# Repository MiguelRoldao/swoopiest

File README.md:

# The Swoopiest

A keyboard based on the iconic [Swoop]() and the adored [Kyria]().

## Gudhowboutya?

## Features
* Soldered universal switch footprint (not hot-swappable)
* Reversible PCB
* Per-key RGB LEDs (mini-e)
* RGB LED underglow
* Up to 2 encoders
* Oled screens
* Power switch for battery management
* Bluetooth support w/ nice!nano or nrf52840
* Tenting puck compatible
* M5 screw holes for cheap tenting

## Components list

To build and use *The Swoopiest* you will need:

* 2× Reversible PCBs
* 2× ProMicro compatible boards or 2 nice!nanos (for headers, the [nrf52840 repo](https://github.com/joric/nrfmicro/wiki/Sockets#machine-pins) has great info)
* 40-42× Keyboard switches
* 40-42× Keycaps 1u
* 40-42× SK6812 Mini-E RGB SMD Leds (optional; not recommended for wireless)
* 40-42× SK6812 3535 RGB SMD Leds (optional; not recommended for wireless)
* 42× diodes (Surface-mount or Through-hole)
* 0-2× Rotary encoders & knobs (optional; ALPS EC11)
* 0-2× OLED LCD Display 128x64 SSD1306 (optional)
* 2× reset switches (optional; (3x6x4.3mm))
* Some little rubber feet/bumpers
* 2× power switches (wireless only; MSK 12C02)
* 2× lipo batteries (wireless only)
* 1× TRRS (See below for more) cable (wired only)
* 2× TRRS Jack [PJ-320A] (wired only)
* 1× USB Cable (depends on your micro-controller choice)  

## Switch compatibility

The universal foot print makes switch incompatibility a thing of the past. The Swoopiest is compatible with most common switch types:
* Choc v1
* Choc v2
* Gateron KS33
* Cherry MX (altough with a bit too much wiggle room. The 5-pin variation fits more snuggly)

With a bit of effort, Reddragon's low profiles also fit by twisting the legs a little bit.

#### The middle pin

The middle pin of the PCB isn't connected to anything (to allow the reversible pcb in conjunction with the universal footprint).
If switches that use the middle pin are chosen (like chocs or reddragons), connect the middle pin to the pads opposite ot the other used pin.
Whether by use of a tiny piece of wire, or with a solder blob.

## Firmware

The firmware is available in my QMK repo as `diaffractus/swoopiest`.  
You can get started by using QMK's [online configurator](https://config.qmk.fm/#/bluebell/swoop/LAYOUT_split_3x5_3). Or check [The Swoopiest README file](https://github.com/MiguelRoldao/qmk-home/blob/master/keyboards/diaffractus/swoopiest/readme.md) to see how to compile the firmware locally.

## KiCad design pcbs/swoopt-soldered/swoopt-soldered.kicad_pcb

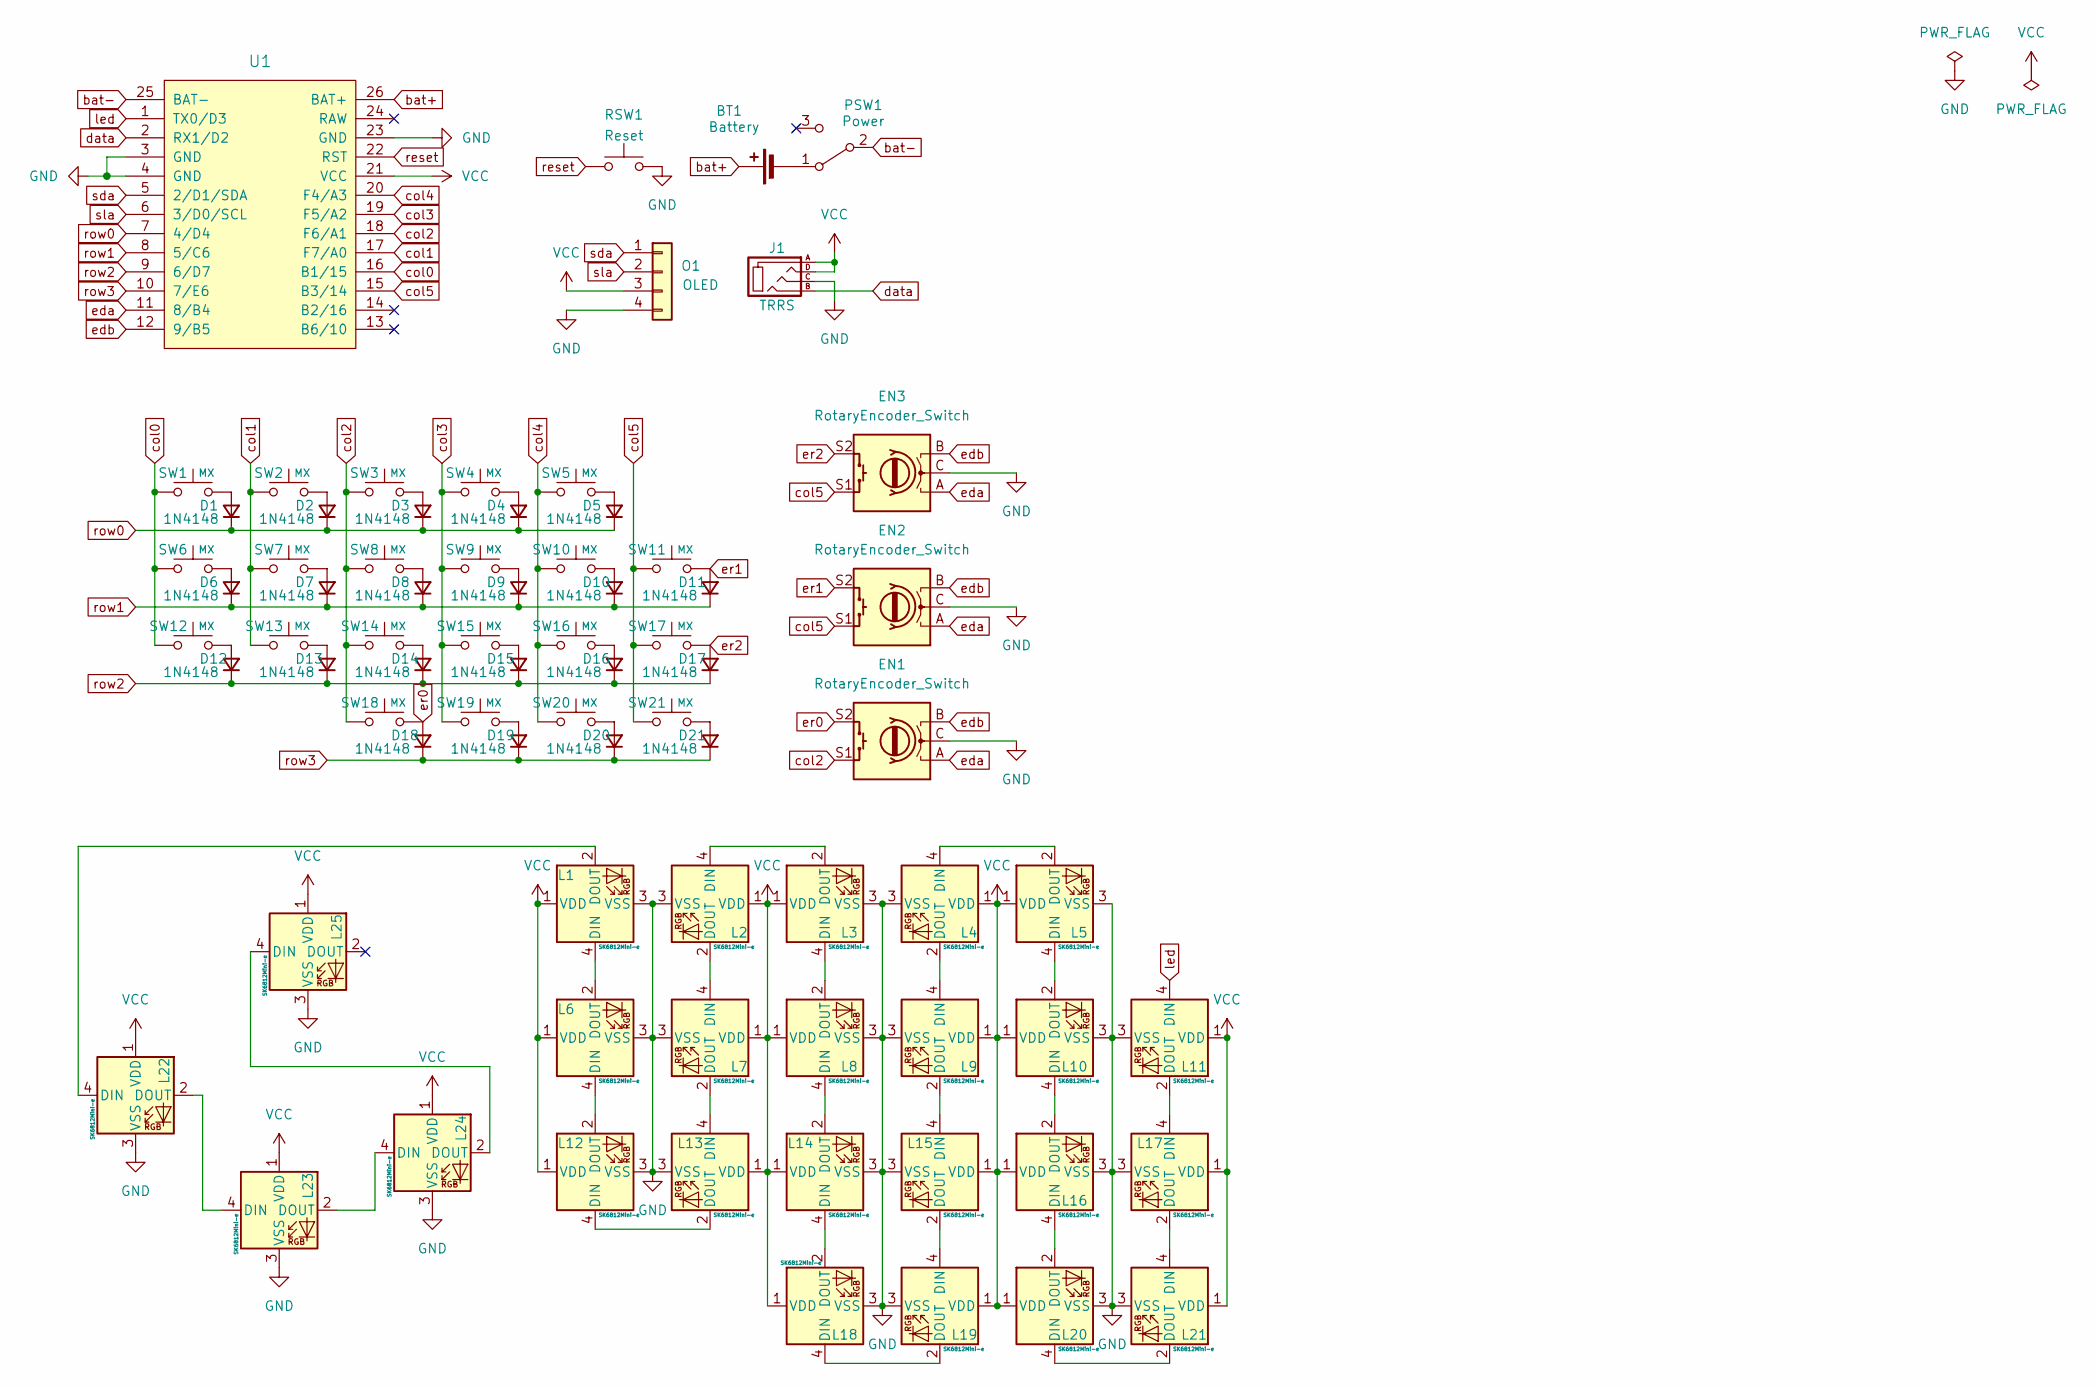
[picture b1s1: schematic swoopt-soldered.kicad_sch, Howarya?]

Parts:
BT1: Battery; Battery_pads_reversible
D1, D2, D3, D4, D5, D6, D7, D8, D9, D10, D11, D12, D13, D14, D15, D16, D17, D18, D19, D20, D21: 1N4148; D_SMD_TH
EN1, EN2, EN3: RotaryEncoder_Switch; RotaryEncoder
J1: TRRS; TRRS-3pin
L1, L2, L3, L4, L5, L6, L7, L8, L9, L10, L11, L12, L13, L14, L15, L16, L17, L18, L19, L20, L21: SK6812Mini-e; SK6812_Mini_E; JLCPCB BOM 0
L22, L23, L24, L25: SK6812Mini-e; LED_SK6812MINI__3.5x3.5mm_reversible; JLCPCB BOM 0
O1: OLED; OLED_jumpers
PSW1: Power
RSW1: Reset; SW_TH_1TS002A
SW1, SW2, SW3, SW4, SW5, SW6, SW7, SW8, SW9, SW10, SW11, SW12, SW13, SW14, SW15, SW16, SW17, SW18, SW19, SW20, SW21: MX; SW_Universal_TH_Reversible
U1: U_ProMicro_nRF52840_TH_Reversible

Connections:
GND: EN1.C, EN2.C, EN3.C, J1.C, L1.3 (VSS), L2.3 (VSS), L3.3 (VSS), L4.3 (VSS), L5.3 (VSS), L6.3 (VSS), L7.3 (VSS), L8.3 (VSS), L9.3 (VSS), L10.3 (VSS), L11.3 (VSS), L12.3 (VSS), L13.3 (VSS), L14.3 (VSS), L15.3 (VSS), L16.3 (VSS), L17.3 (VSS), L18.3 (VSS), L19.3 (VSS), L20.3 (VSS), L21.3 (VSS), L22.3 (VSS), L23.3 (VSS), L24.3 (VSS), L25.3 (VSS), O1.4, RSW1.2, U1.3 (GND), U1.4 (GND), U1.23 (GND); also elsewhere on the board
unnamed: BT1.2 (-), PSW1.1 (A)
unnamed: D1.2 (A), SW1.2
unnamed: D2.2 (A), SW2.2
unnamed: D3.2 (A), SW3.2
unnamed: D4.2 (A), SW4.2
unnamed: D5.2 (A), SW5.2
unnamed: D6.2 (A), SW6.2
unnamed: D7.2 (A), SW7.2
unnamed: D8.2 (A), SW8.2
unnamed: D9.2 (A), SW9.2
unnamed: D10.2 (A), SW10.2
unnamed: D12.2 (A), SW12.2
unnamed: D13.2 (A), SW13.2
unnamed: D14.2 (A), SW14.2
unnamed: D15.2 (A), SW15.2
unnamed: D16.2 (A), SW16.2
unnamed: D19.2 (A), SW19.2
unnamed: D20.2 (A), SW20.2
unnamed: D21.2 (A), SW21.2
unnamed: L1.4 (DIN), L6.2 (DOUT)
unnamed: L1.2 (DOUT), L22.4 (DIN)
unnamed: L2.4 (DIN), L3.2 (DOUT)
unnamed: L2.2 (DOUT), L7.4 (DIN)
unnamed: L3.4 (DIN), L8.2 (DOUT)
unnamed: L4.4 (DIN), L5.2 (DOUT)
unnamed: L4.2 (DOUT), L9.4 (DIN)
unnamed: L10.4 (DIN), L16.2 (DOUT)
unnamed: L5.4 (DIN), L10.2 (DOUT)
unnamed: L11.2 (DOUT), L17.4 (DIN)
unnamed: L12.4 (DIN), L13.2 (DOUT)
unnamed: L6.4 (DIN), L12.2 (DOUT)
unnamed: L7.2 (DOUT), L13.4 (DIN)
unnamed: L14.4 (DIN), L18.2 (DOUT)
unnamed: L8.4 (DIN), L14.2 (DOUT)
unnamed: L9.2 (DOUT), L15.4 (DIN)
unnamed: L15.2 (DOUT), L19.4 (DIN)
unnamed: L16.4 (DIN), L20.2 (DOUT)
unnamed: L17.2 (DOUT), L21.4 (DIN)
unnamed: L18.4 (DIN), L19.2 (DOUT)
unnamed: L20.4 (DIN), L21.2 (DOUT)
unnamed: L22.2 (DOUT), L23.4 (DIN)
unnamed: L23.2 (DOUT), L24.4 (DIN)
unnamed: L24.2 (DOUT), L25.4 (DIN)
VCC: J1.A, J1.D, L1.1 (VDD), L2.1 (VDD), L3.1 (VDD), L4.1 (VDD), L5.1 (VDD), L6.1 (VDD), L7.1 (VDD), L8.1 (VDD), L9.1 (VDD), L10.1 (VDD), L11.1 (VDD), L12.1 (VDD), L13.1 (VDD), L14.1 (VDD), L15.1 (VDD), L16.1 (VDD), L17.1 (VDD), L18.1 (VDD), L19.1 (VDD), L20.1 (VDD), L21.1 (VDD), L22.1 (VDD), L23.1 (VDD), L24.1 (VDD), L25.1 (VDD), O1.3, U1.21 (VCC); also elsewhere on the board
bat+: BT1.1 (+), U1.26 (BAT+)
bat-: PSW1.2 (B), U1.25 (BAT-)
col0: SW1.1, SW6.1, SW12.1, U1.16 (B1/15)
col1: SW2.1, SW7.1, SW13.1, U1.17 (F7/A0)
col2: EN1.S1, SW3.1, SW8.1, SW14.1, SW18.1, U1.18 (F6/A1)
col3: SW4.1, SW9.1, SW15.1, SW19.1, U1.19 (F5/A2)
col4: SW5.1, SW10.1, SW16.1, SW20.1, U1.20 (F4/A3)
col5: EN2.S1, EN3.S1, SW11.1, SW17.1, SW21.1, U1.15 (B3/14)
data: J1.B, U1.2 (RX1/D2); also elsewhere on the board
eda: EN1.A, EN2.A, EN3.A, U1.11 (8/B4)
edb: EN1.B, EN2.B, EN3.B, U1.12 (9/B5)
er0: D18.2 (A), EN1.S2, SW18.2
er1: D11.2 (A), EN2.S2, SW11.2
er2: D17.2 (A), EN3.S2, SW17.2
led: L11.4 (DIN), U1.1 (TX0/D3)
reset: RSW1.1, U1.22 (RST)
row0: D1.1 (K), D2.1 (K), D3.1 (K), D4.1 (K), D5.1 (K), U1.7 (4/D4)
row1: D6.1 (K), D7.1 (K), D8.1 (K), D9.1 (K), D10.1 (K), D11.1 (K), U1.8 (5/C6)
row2: D12.1 (K), D13.1 (K), D14.1 (K), D15.1 (K), D16.1 (K), D17.1 (K), U1.9 (6/D7)
row3: D18.1 (K), D19.1 (K), D20.1 (K), D21.1 (K), U1.10 (7/E6)
sda: O1.1, U1.5 (2/D1/SDA)
sla: O1.2, U1.6 (3/D0/SCL)

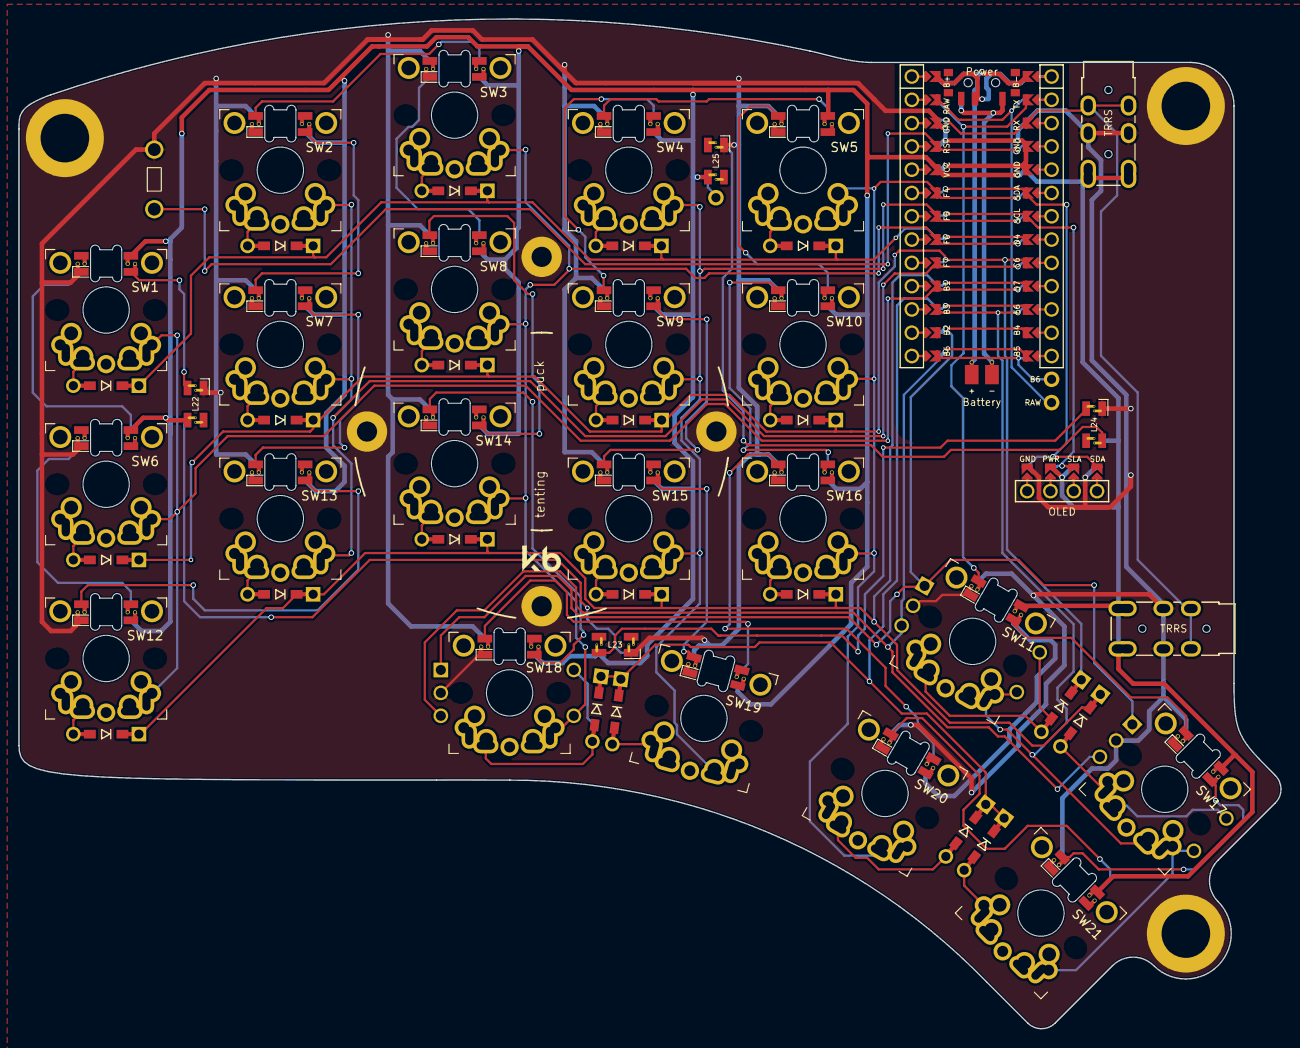
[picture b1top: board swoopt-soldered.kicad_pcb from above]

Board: 2 copper layers, 137.6 x 110.1 mm, 77 parts (1 on the bottom side), 67 nets.

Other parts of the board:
J1#2: TRRS; TRRS-3pin

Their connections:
GND: J1#2.C; also elsewhere on the board
VCC: J1#2.A, J1#2.D; also elsewhere on the board
data: J1#2.B; also elsewhere on the board

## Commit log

2025-09-16 updated footprints and traces. Also added Debora.
2025-09-26 added gerbers and missing libraries
2025-09-26 work on the swoopiest - layout defined
2025-09-27 traces are complete, with second jack
2025-09-30 added underglow leds
2025-10-01 added tenting screw holes, with needed board alterations
2025-10-01 added m2 screw holes for mounting
2025-10-01 pulled pinky column 2mm down
2025-10-01 added tenting puck
2025-10-26 minor adjustments to pcb
2025-10-27 Added a needed readme
2025-10-28 fixed README link to qmk
